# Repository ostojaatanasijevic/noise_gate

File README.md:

# TPI pedals - BMF

## Schematic

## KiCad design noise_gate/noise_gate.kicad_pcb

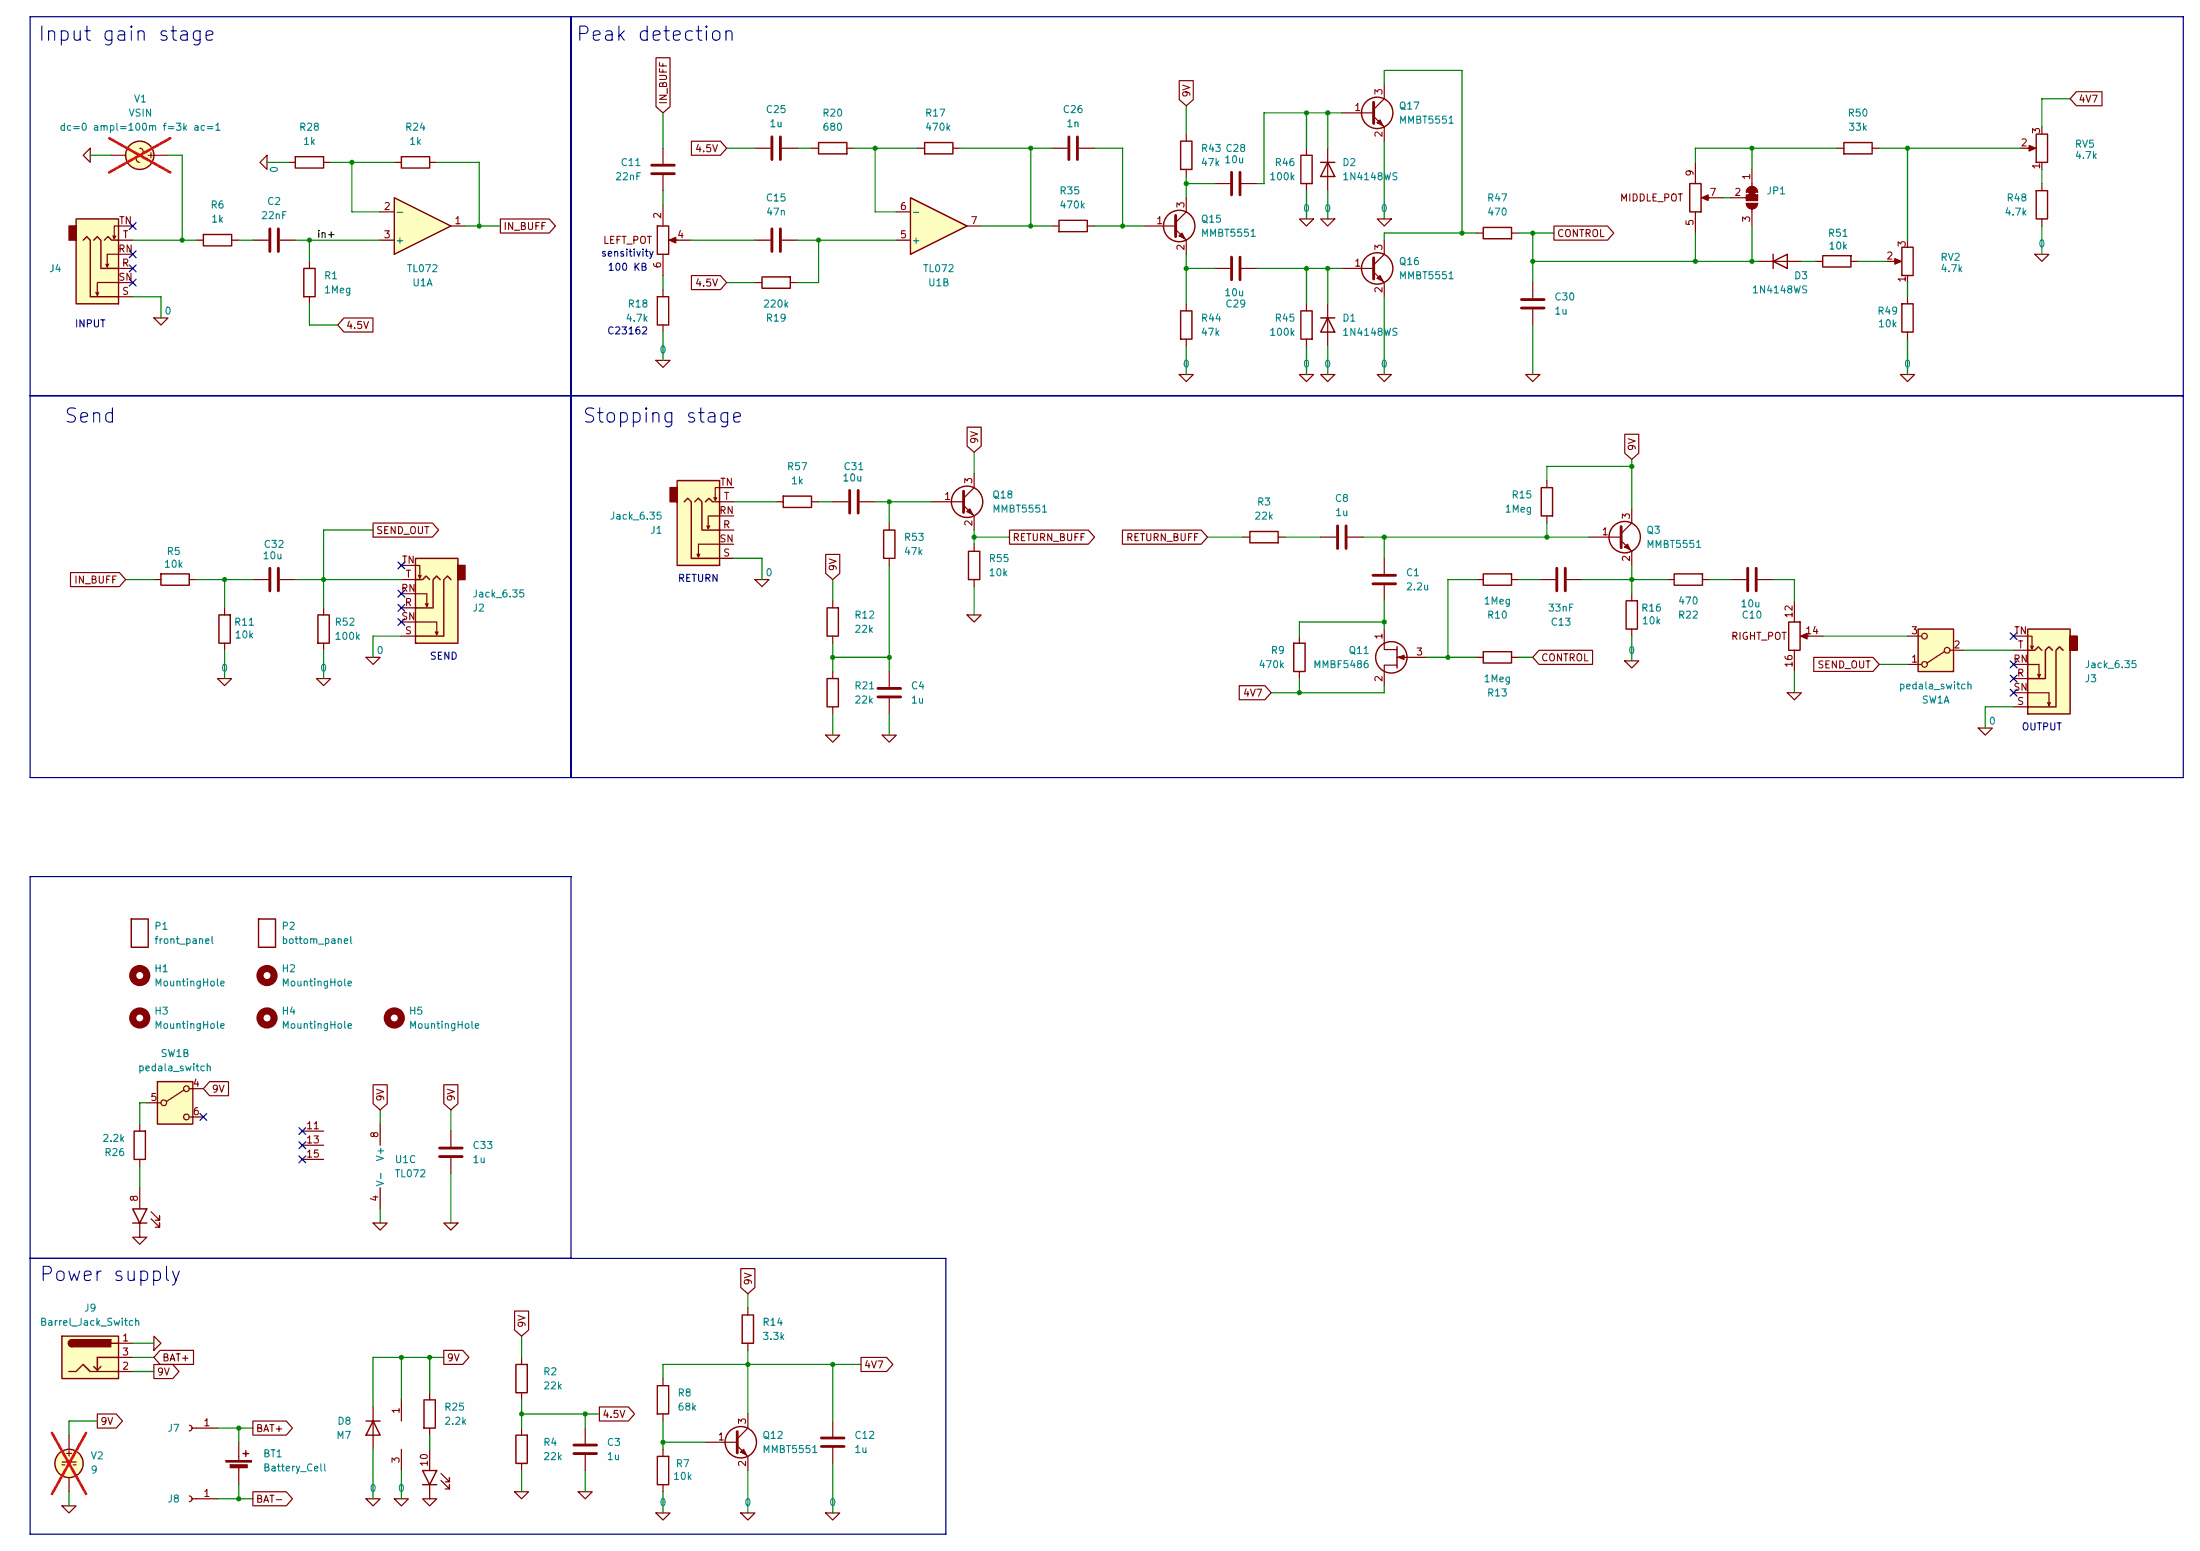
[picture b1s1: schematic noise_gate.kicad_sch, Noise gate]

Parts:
BT1: Battery_Cell; BatteryHolder_Eagle_12BH611-GR
C1: 2.2u; C_0603_1608Metric_Pad1.08x0.95mm_HandSolder; LCSC C21122
C2, C11: 22nF; C_0603_1608Metric_Pad1.08x0.95mm_HandSolder; LCSC C21122
C3, C4, C8, C12, C25, C30, C33: 1u; C_0603_1608Metric_Pad1.08x0.95mm_HandSolder; LCSC C15849
C10, C28, C29, C31, C32: 10u; C_0603_1608Metric_Pad1.08x0.95mm_HandSolder; LCSC C96446
C13: 33nF; C_0603_1608Metric_Pad1.08x0.95mm_HandSolder; LCSC C1614
C15: 47n; C_0603_1608Metric_Pad1.08x0.95mm_HandSolder; LCSC C1622
C26: 1n; C_0603_1608Metric_Pad1.08x0.95mm_HandSolder; LCSC C1588
D1, D2, D3: 1N4148WS; D_SOD-323; LCSC C2128
D8: M7; D_SMA; LCSC C95872
H1, H2, H3, H4, H5: MountingHole; M3_hole_with_spacer
J1, J2, J3, J4: Jack_6.35; Jack_6.35mm
J6: top_panel_connector; IDC-Header_2x08_P2.54mm_Vertical
J7, J8: Conn_01x01_Socket; TestPoint_THTPad_D2.5mm_Drill1.2mm
J9: Barrel_Jack_Switch; BarrelJack
JP1: SolderJumper_3_Bridged12; SolderJumper-3_P1.3mm_Bridged12_Pad1.0x1.5mm
P1: front_panel; front_plate
P2: bottom_panel; bottom_plate
Q3, Q12, Q15, Q16, Q17, Q18: MMBT5551; SOT-23; LCSC C2145
Q11: MMBF5486; SOT-23
R1, R10, R13, R15: 1Meg; R_0603_1608Metric_Pad0.98x0.95mm_HandSolder; LCSC C25819
R2, R3, R4, R12, R21: 22k; R_0603_1608Metric_Pad0.98x0.95mm_HandSolder; LCSC C31850
R5, R7, R11, R16, R49, R51, R55: 10k; R_0603_1608Metric_Pad0.98x0.95mm_HandSolder; LCSC C25804
R6, R24, R28, R57: 1k; R_0603_1608Metric_Pad0.98x0.95mm_HandSolder; LCSC C21190
R8: 68k; R_0603_1608Metric_Pad0.98x0.95mm_HandSolder; LCSC C23231
R9, R17, R35: 470k; R_0603_1608Metric_Pad0.98x0.95mm_HandSolder; LCSC C23178
R14: 3.3k; R_0603_1608Metric_Pad0.98x0.95mm_HandSolder; LCSC C22978
R18, R48: 4.7k; R_0603_1608Metric_Pad0.98x0.95mm_HandSolder; LCSC C23162
R19: 220k; R_0603_1608Metric_Pad0.98x0.95mm_HandSolder; LCSC C22961
R20: 680; R_0603_1608Metric_Pad0.98x0.95mm_HandSolder; LCSC C23228
R22, R47: 470; R_0603_1608Metric_Pad0.98x0.95mm_HandSolder; LCSC C23179
R25, R26: 2.2k; R_0603_1608Metric_Pad0.98x0.95mm_HandSolder; LCSC C4190
R43, R44, R53: 47k; R_0603_1608Metric_Pad0.98x0.95mm_HandSolder; LCSC C25819
R45, R46, R52: 100k; R_0603_1608Metric_Pad0.98x0.95mm_HandSolder; LCSC C25803
R50: 33k; R_0603_1608Metric_Pad0.98x0.95mm_HandSolder; LCSC C4216
RV2, RV5: 4.7k; Potentiometer_Bourns_3296W_Vertical
SW1: pedala_switch; foot_switch_tht_no_pad
U1: TL072; SOIC-8_3.9x4.9mm_P1.27mm
V1: VSIN; not fitted
V2: 9; not fitted

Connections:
0: C3.1, C4.1, C12.1, C30.1, C33.1, D1.2 (A), D2.2 (A), D8.2 (A), J1.S, J2.S, J3.S, J4.S, J6.3 (GND), J6.16, J9.1, Q12.2 (E), Q16.2 (E), Q17.2 (E), R4.1, R7.1, R11.1, R16.1, R18.1, R21.1, R28.2, R44.2, R45.2, R46.2, R48.1, R49.1, R52.2, R55.2, U1.4 (V-), V1.2, V2.2
4.5V: C3.2, C25.1, R1.2, R2.1, R4.2, R19.1
4V7: C12.2, Q11.2 (S), Q12.3 (C), R8.1, R9.1, R14.2, RV5.3
9V: C33.2, D8.1 (K), J6.1 (VCC), J9.2, Q3.3 (C), Q18.3 (C), R2.2, R12.2, R14.1, R15.1, R25.1, R43.1, SW1.4 (A), U1.8 (V+), V2.1
/in+: C2.2, R1.1, U1.3 (+)
BAT+: BT1.1 (+), J7.1, J9.3
BAT-: BT1.2 (-), J8.1
CONTROL: C30.2, D3.1 (K), J6.5, JP1.3 (B), R13.2, R47.2
IN_BUFF: C11.2, R5.2, R24.1, U1.1
unnamed: C2.1, R6.1
unnamed: C4.2, R12.1, R21.2, R53.2
unnamed: C8.1, R3.2
unnamed: C10.1, R22.2
unnamed: C13.1, R10.2
unnamed: C25.2, R20.1
unnamed: C26.1, R17.1, R35.2, U1.7
unnamed: C31.1, R57.1
unnamed: C32.1, R5.1, R11.2
unnamed: C29.2, D1.1 (K), Q16.1 (B), R45.1
unnamed: C28.2, D2.1 (K), Q17.1 (B), R46.1
unnamed: D3.2 (A), R51.1
unnamed: J1.T, R57.2
unnamed: J4.T, R6.2, V1.1
unnamed: C11.1, J6.2
unnamed: C15.1, J6.4
unnamed: J6.6, R18.2
unnamed: J6.7, JP1.2 (C)
unnamed: J6.9, JP1.1 (A), R50.2
unnamed: C10.2, J6.12
unnamed: J6.14, SW1.3 (C)
unnamed: J6.8, R26.1
unnamed: J6.10, R25.2
unnamed: C1.2, C8.2, Q3.1 (B), R15.2
unnamed: C13.2, Q3.2 (E), R16.2, R22.1
unnamed: C1.1, Q11.1 (D), R9.2
unnamed: Q11.3 (G), R10.1, R13.1
unnamed: Q12.1 (B), R7.2, R8.2
unnamed: C26.2, Q15.1 (B), R35.1
unnamed: C28.1, Q15.3 (C), R43.2
unnamed: C29.1, Q15.2 (E), R44.1
unnamed: Q16.3 (C), Q17.3 (C), R47.1
unnamed: C31.2, Q18.1 (B), R53.1
unnamed: R48.2, RV5.1
unnamed: R49.2, RV2.1
unnamed: R50.1, RV2.3, RV5.2
unnamed: R51.2, RV2.2
unnamed: J3.T, SW1.2 (B)
unnamed: R26.2, SW1.5 (B)
unnamed: R24.2, R28.1, U1.2 (-)
unnamed: C15.2, R19.2, U1.5 (+)
unnamed: R17.2, R20.2, U1.6 (-)
RETURN_BUFF: Q18.2 (E), R3.1, R55.1
SEND_OUT: C32.2, J2.T, R52.1, SW1.1 (A)

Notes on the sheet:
Peak detection
sensitivity
RETURN
INPUT
SEND
Input gain stage
C23162
100 KB
Send
Stopping stage
Power supply
OUTPUT

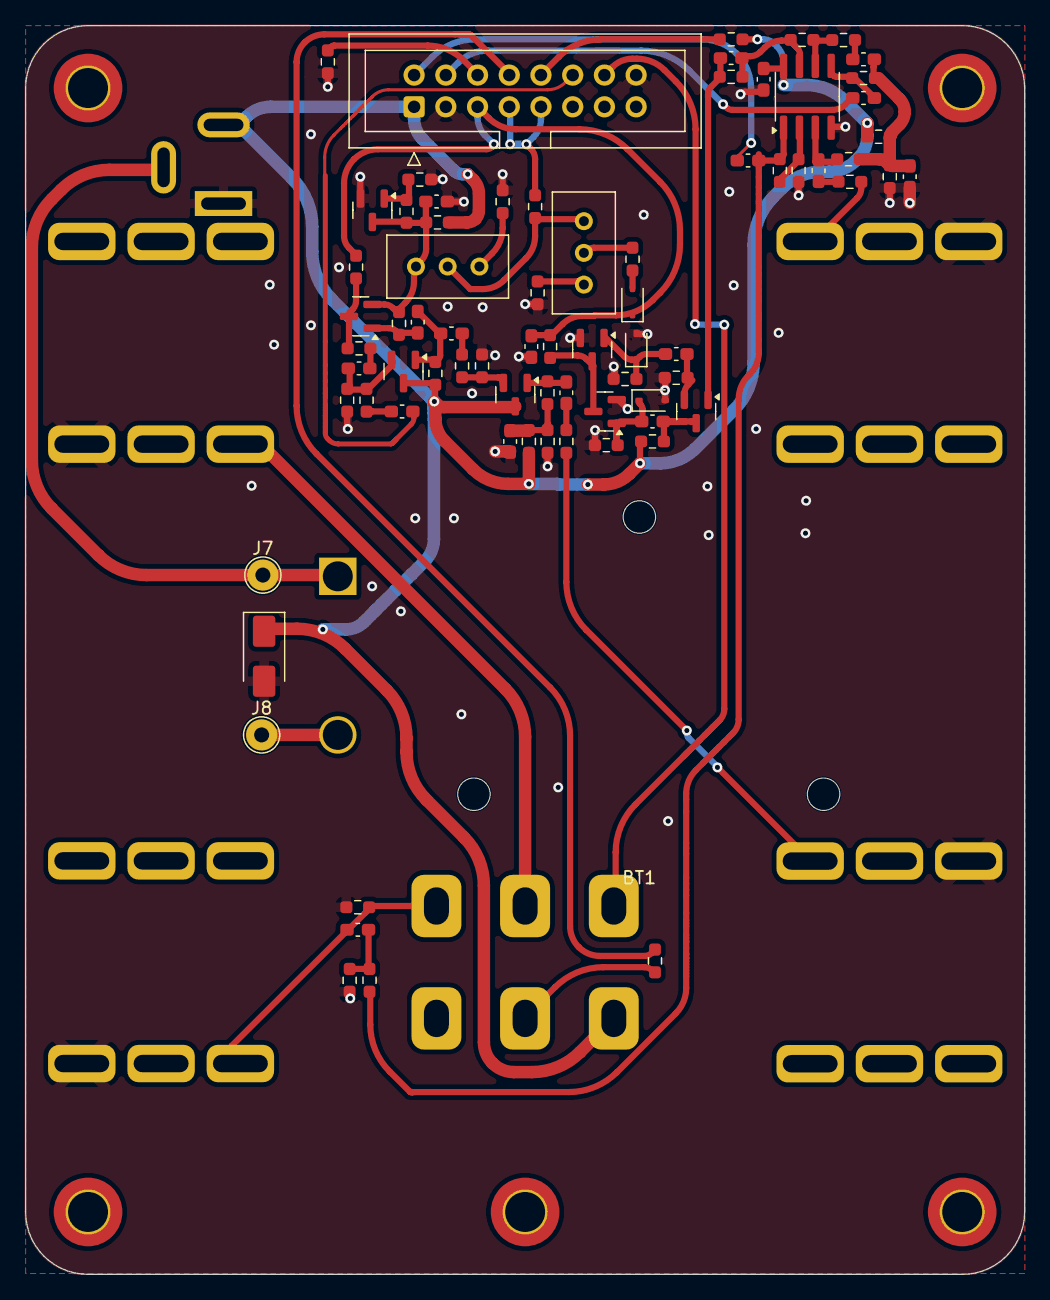
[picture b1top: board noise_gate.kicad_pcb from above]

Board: 2 copper layers, 80.0 x 100.0 mm, 90 parts (1 on the bottom side), 53 nets.

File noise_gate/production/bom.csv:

Designator,Footprint,Quantity,Value,LCSC Part #
BT1,BatteryHolder_Eagle_12BH611-GR,1,Battery_Cell,
C1,0603,1,2.2u,C21122
"C10, C28, C29, C31, C32",0603,5,10u,C96446
"C11, C2",0603,2,22nF,C21122
"C12, C25, C3, C30, C33, C4, C8",0603,7,1u,C15849
C13,0603,1,33nF,C1614
C15,0603,1,47n,C1622
C26,0603,1,1n,C1588
"D1, D2, D3",D_SOD-323,3,1N4148WS,C2128
D8,D_SMA,1,M7,C95872
"H1, H2, H3, H4, H5",M3_hole_with_spacer,5,MountingHole,
"J1, J2, J3, J4",Jack_6.35mm,4,Jack_6.35,
J6,IDC-Header_2x08_P2.54mm_Vertical,1,top_panel_connector,
"J7, J8",TestPoint_THTPad_D2.5mm_Drill1.2mm,2,Conn_01x01_Socket,
J9,BarrelJack,1,Barrel_Jack_Switch,
P1,front_plate,1,front_panel,
P2,bottom_plate,1,bottom_panel,
Q11,SOT-23,1,MMBF5486,
"Q12, Q15, Q16, Q17, Q18, Q3",SOT-23,6,MMBT5551,C2145
"R1, R10, R13, R15",0603,4,1Meg,C25819
"R11, R16, R49, R5, R51, R55, R7",0603,7,10k,C25804
"R12, R2, R21, R3, R4",0603,5,22k,C31850
R14,0603,1,3.3k,C22978
"R17, R35, R9",0603,3,470k,C23178
"R18, R48",0603,2,4.7k,C23162
R19,0603,1,220k,C22961
R20,0603,1,680,C23228
"R22, R47",0603,2,470,C23179
"R24, R28, R57, R6",0603,4,1k,C21190
"R25, R26",0603,2,2.2k,C4190
"R43, R44, R53",0603,3,47k,C25819
"R45, R46, R52",0603,3,100k,C25803
R50,0603,1,33k,C4216
R8,0603,1,68k,C23231
"RV2, RV5",Potentiometer_Bourns_3296W_Vertical,2,4.7k,
SW1,foot_switch_tht_no_pad,1,pedala_switch,
U1,SOIC-8_3.9x4.9mm_P1.27mm,1,TL072,

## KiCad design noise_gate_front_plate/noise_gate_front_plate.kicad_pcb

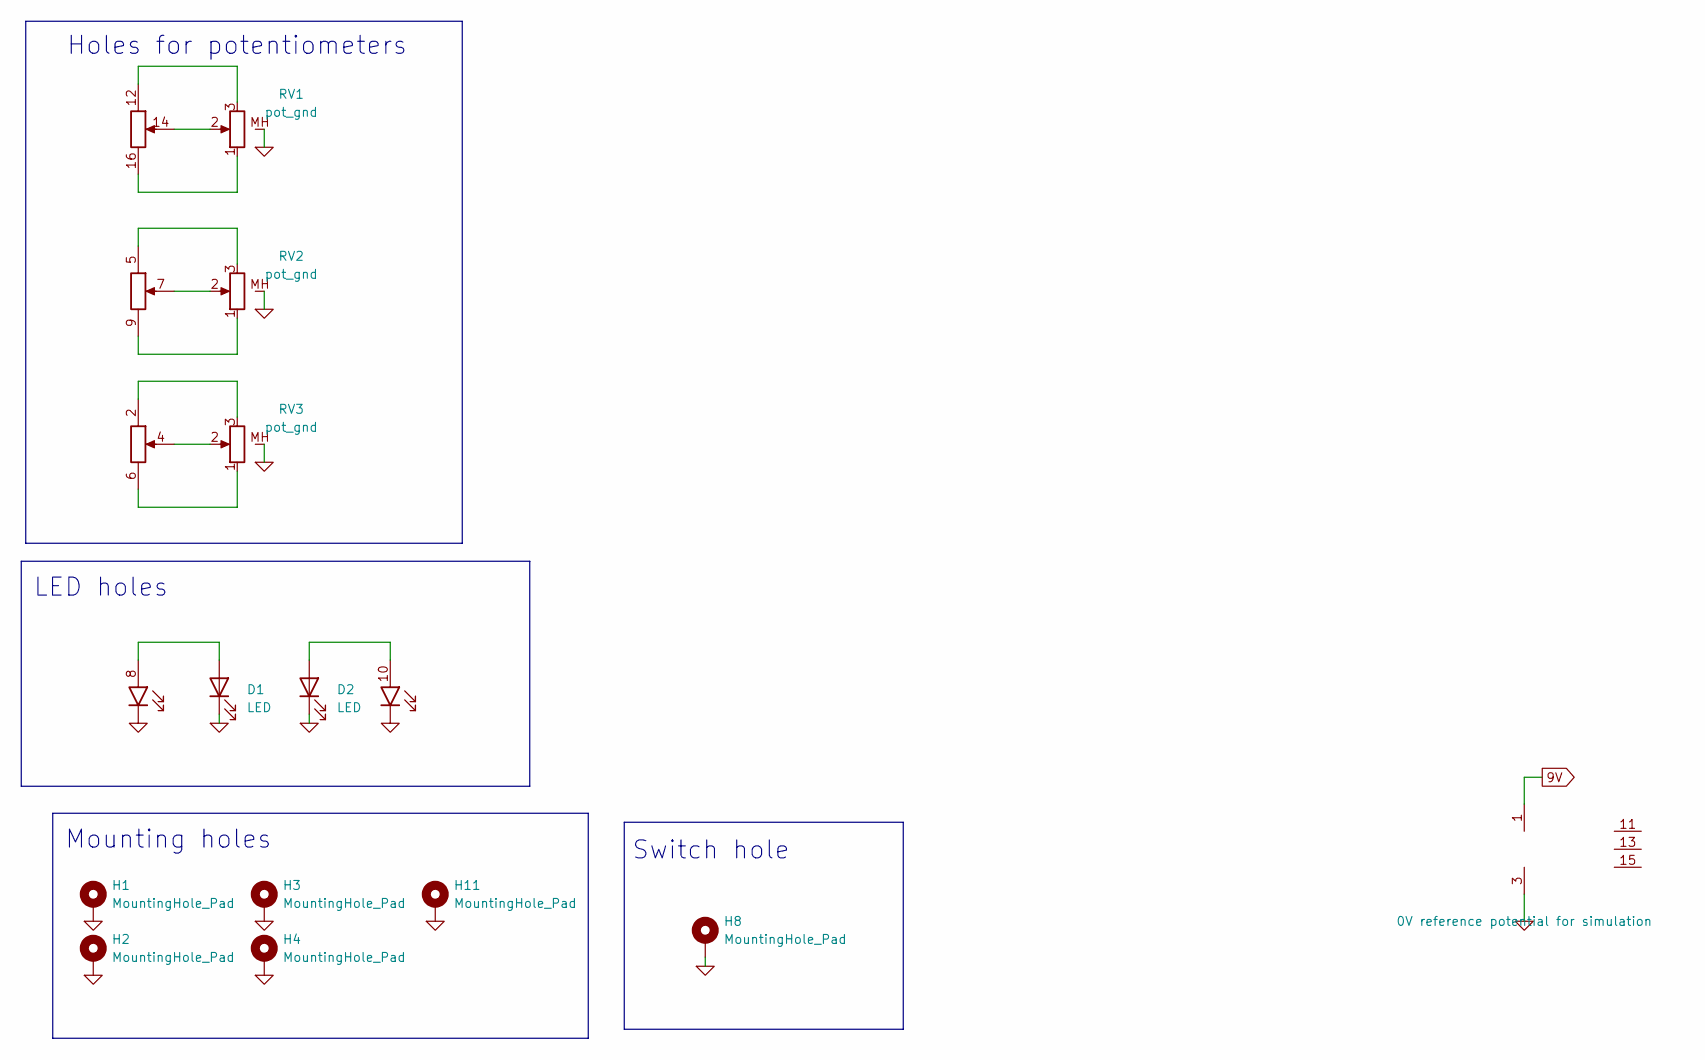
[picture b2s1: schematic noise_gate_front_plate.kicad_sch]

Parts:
D1: LED; red_led
D2: LED; green_led
H1, H2, H3, H4, H11: MountingHole_Pad; MountingHole_3.2mm_M3_DIN965_Pad_TopBottom
H8: MountingHole_Pad; plated_switch_hole
J1: top_panel_connector; IDC-Header_2x08_faux_SMD
RV1, RV2, RV3: pot_gnd; top_plate_pot

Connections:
0: D1.1 (K), D2.1 (K), H1.1, H2.1, H3.1, H4.1, H8.1, H11.1, J1.3 (GND), RV1.MH (2), RV2.MH (2), RV3.MH (2)
9V: J1.1 (VCC)
unnamed: D1.2 (A), J1.8
unnamed: D2.2 (A), J1.10
unnamed: J1.2, RV3.3
unnamed: J1.4, RV3.2
unnamed: J1.6, RV3.1
unnamed: J1.5, RV2.3
unnamed: J1.7, RV2.2
unnamed: J1.9, RV2.1
unnamed: J1.12, RV1.3
unnamed: J1.14, RV1.2
unnamed: J1.16, RV1.1

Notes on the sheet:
Mounting holes
Switch hole
LED holes
Holes for potentiometers

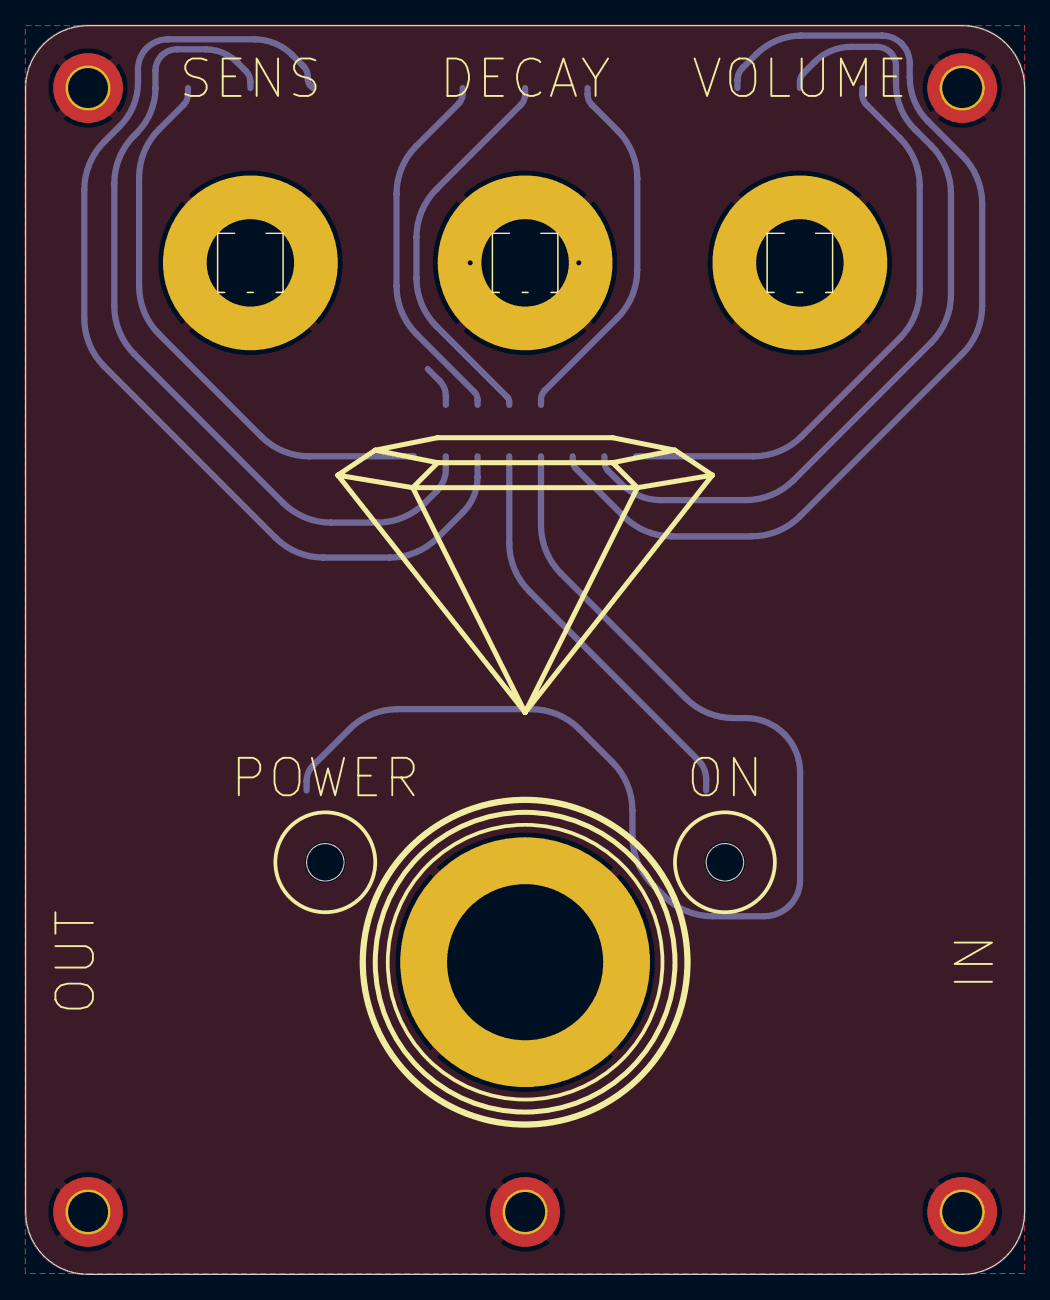
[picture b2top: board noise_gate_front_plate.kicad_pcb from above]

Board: 2 copper layers, 80.0 x 100.0 mm, 12 parts (1 on the bottom side), 12 nets.

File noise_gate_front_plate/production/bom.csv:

Designator,Footprint,Quantity,Value,LCSC Part #
D1,red_led,1,LED,
D2,green_led,1,LED,
"H1, H11, H2, H3, H4",MountingHole_3.2mm_M3_DIN965_Pad_TopBottom,5,MountingHole_Pad,
J1,IDC-Header_2x08_faux_SMD,1,top_panel_connector,
"RV1, RV2, RV3",top_plate_pot,3,pot_gnd,

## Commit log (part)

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2025-05-28 Cloned the BMF, noise gate init.
2025-06-01 White pcbs.
2025-06-01 3d bodies.
